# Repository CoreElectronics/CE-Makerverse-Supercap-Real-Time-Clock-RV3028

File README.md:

# Makerverse™ Supercap Real Time Clcok

This is the repo for the Core Electronics [Makerverse supercap Real Time Clock](https://core-electronics.com.au/catalog/product/view/sku/ce07922).

The PCB layout project requires KiCAD 5.99 or newer to view. The schematic and PCB are both provided in PDF format in the Documents folder.

## License
This project is open source - please review the LICENSE.md file for further licensing information.

If you have any technical questions, or concerns about licensing, please contact technical support on the [Core Electronics forums](https://forum.core-electronics.com.au/).

*\"Makerverse\" and the Makerverse logo are trademarks of Core Electronics Pty Ltd.*

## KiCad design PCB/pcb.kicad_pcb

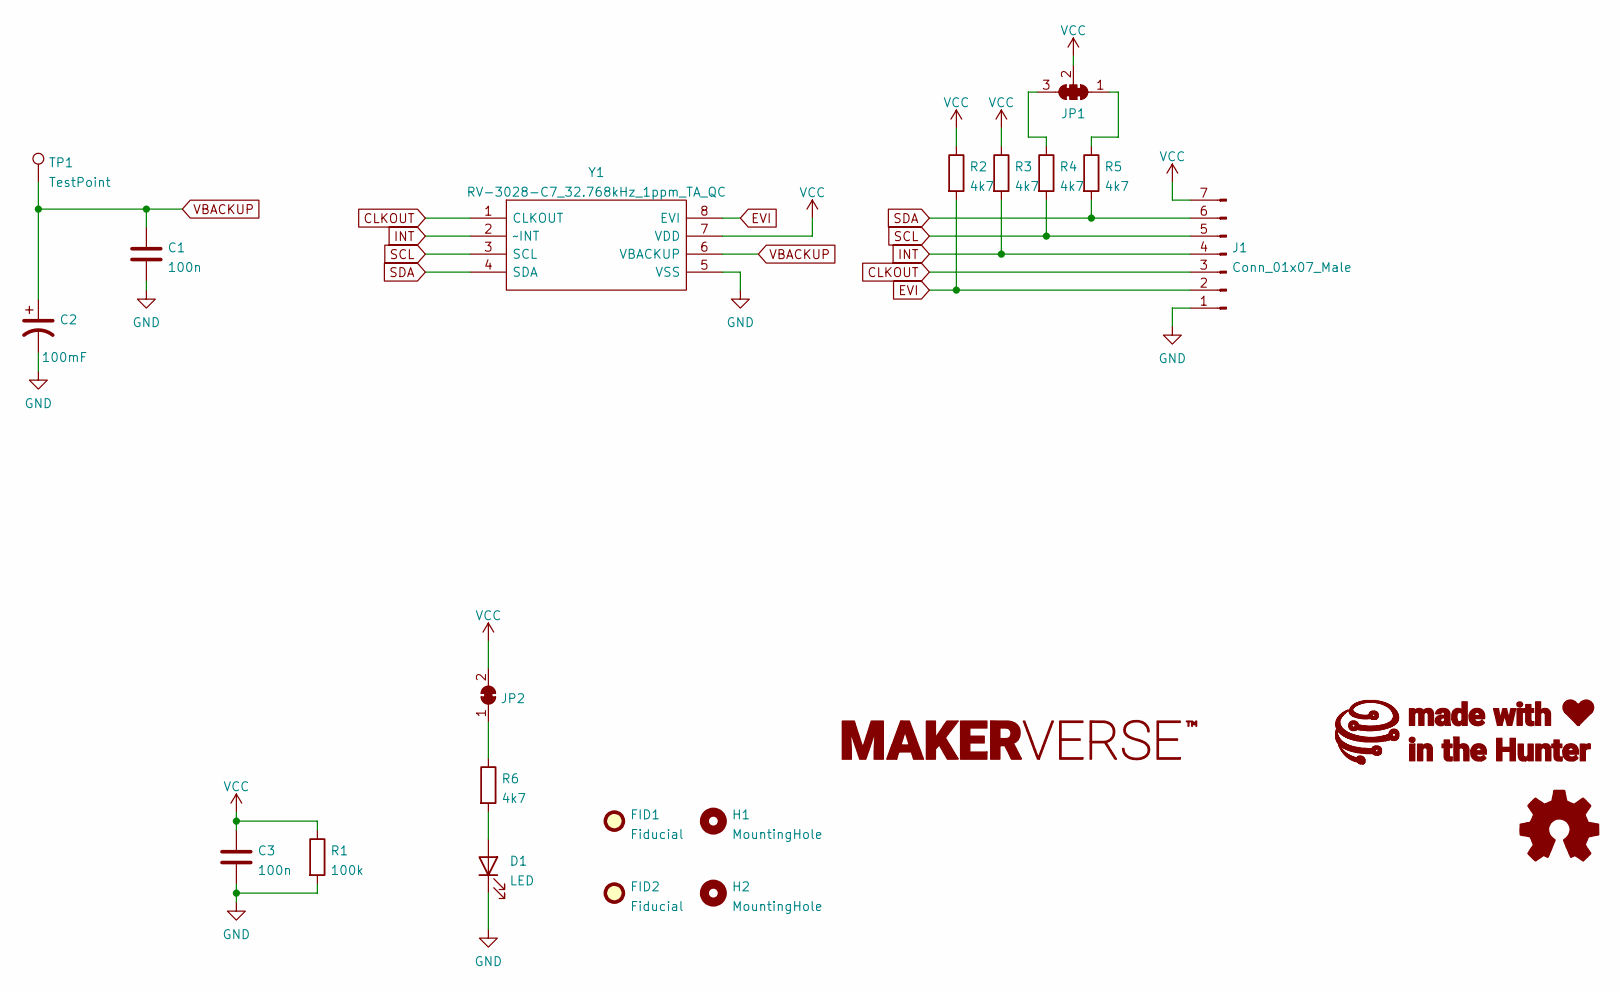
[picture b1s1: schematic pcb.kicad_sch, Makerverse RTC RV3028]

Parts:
C1, C3: 100n; C_0402_1005Metric
C2: 100mF; FC_10.5X5.5_
D1: LED; LED_0603_1608Metric
FID1, FID2: Fiducial; Fiducial_1mm_Mask2mm
H1, H2: MountingHole; MountingHole_3.2mm_M3
J1: Conn_01x07_Male; PinSocket_1x07_P2.54mm_Vertical
JP1: SolderJumper_3_Bridged123; SolderJumper-3_P1.3mm_Closed_RoundedPad1.0x1.5mm
JP2: SolderJumper_2_Bridged; SolderJumper-2_P1.3mm_Bridged_RoundedPad1.0x1.5mm
R1: 100k; R_0402_1005Metric
R2, R3, R4, R5, R6: 4k7; R_0402_1005Metric
TP1: TestPoint; TestPoint_THTPad_D1.5mm_Drill0.7mm
Y1: RV-3028-C7_32.768kHz_1ppm_TA_QC; RV3028C732768kHz1ppmTAQC; Mouser Part Number 428-203591-MG01

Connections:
CLKOUT: J1.3, Y1.1 (CLKOUT)
EVI: J1.2, R2.2, Y1.8 (EVI)
GND: C1.2, C2.2, C3.2, D1.1 (K), J1.1, R1.2, Y1.5 (VSS)
INT: J1.4, R3.2, Y1.2 (~INT)
unnamed: D1.2 (A), R6.2
unnamed: JP1.1 (A), R5.1
unnamed: JP1.3 (B), R4.1
unnamed: JP2.1 (A), R6.1
SCL: J1.5, R4.2, Y1.3 (SCL)
SDA: J1.6, R5.2, Y1.4 (SDA)
VBACKUP: C1.1, C2.1, TP1.1, Y1.6 (VBACKUP)
VCC: C3.1, J1.7, JP1.2 (C), JP2.2 (B), R1.1, R2.1, R3.1, Y1.7 (VDD)

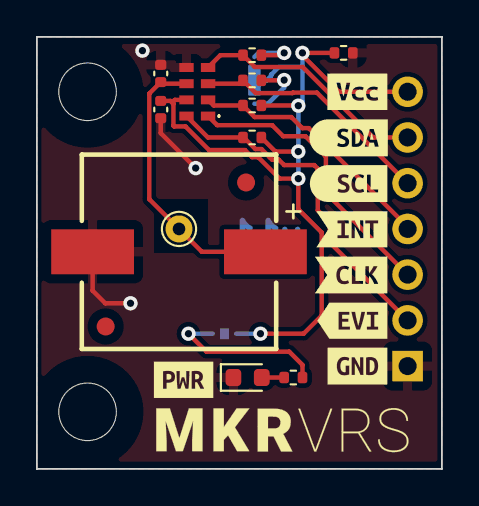
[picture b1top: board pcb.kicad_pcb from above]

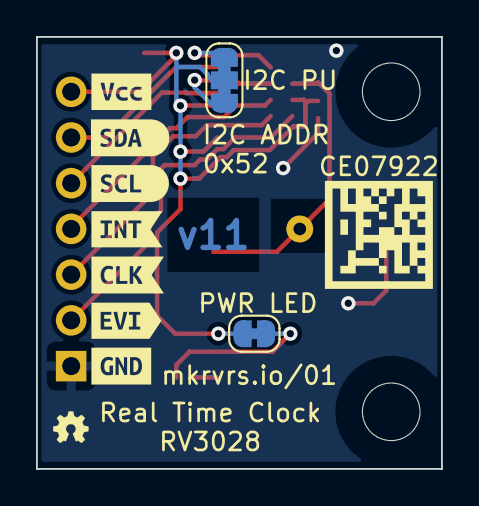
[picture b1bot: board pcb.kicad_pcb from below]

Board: 2 copper layers, 22.5 x 24.0 mm, 35 parts (9 on the bottom side), 12 nets.

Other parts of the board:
G1: LOGO; makerverse_logo_short_14.0x2.4mm
kibuzzard-610A0DD3: G***; kibuzzard-610A0DD3
kibuzzard-611F2ECA: G***; kibuzzard-611F2ECA
kibuzzard-611F2EE3: G***; kibuzzard-611F2EE3
kibuzzard-611F2EF5: G***; kibuzzard-611F2EF5
kibuzzard-611F2F08: G***; kibuzzard-611F2F08
kibuzzard-611F2F8F: G***; kibuzzard-611F2F8F
kibuzzard-611F2F9E: G***; kibuzzard-611F2F9E
kibuzzard-611F2FAD: G***; kibuzzard-611F2FAD
kibuzzard-611F2FF6: G***; kibuzzard-611F2FF6
kibuzzard-611F3003: G***; kibuzzard-611F3003
kibuzzard-611F3011: G***; kibuzzard-611F3011
kibuzzard-6109FC7A, kibuzzard-6109FC7A#2: G***; kibuzzard-6109FC7A
kibuzzard-6109FD62, kibuzzard-6109FD62#2: G***; kibuzzard-6109FD62

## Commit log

2021-12-07 Initial commit.
2021-12-07 Pre-publish commit.

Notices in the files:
PCB/pcb.kicad_pcb:
License: CCASAv4.0 https://creativecommons.org/licenses/by-sa/4.0
